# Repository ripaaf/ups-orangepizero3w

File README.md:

# ups-orangepizero3w
trying making a pcb ups for orangepi (its bad)

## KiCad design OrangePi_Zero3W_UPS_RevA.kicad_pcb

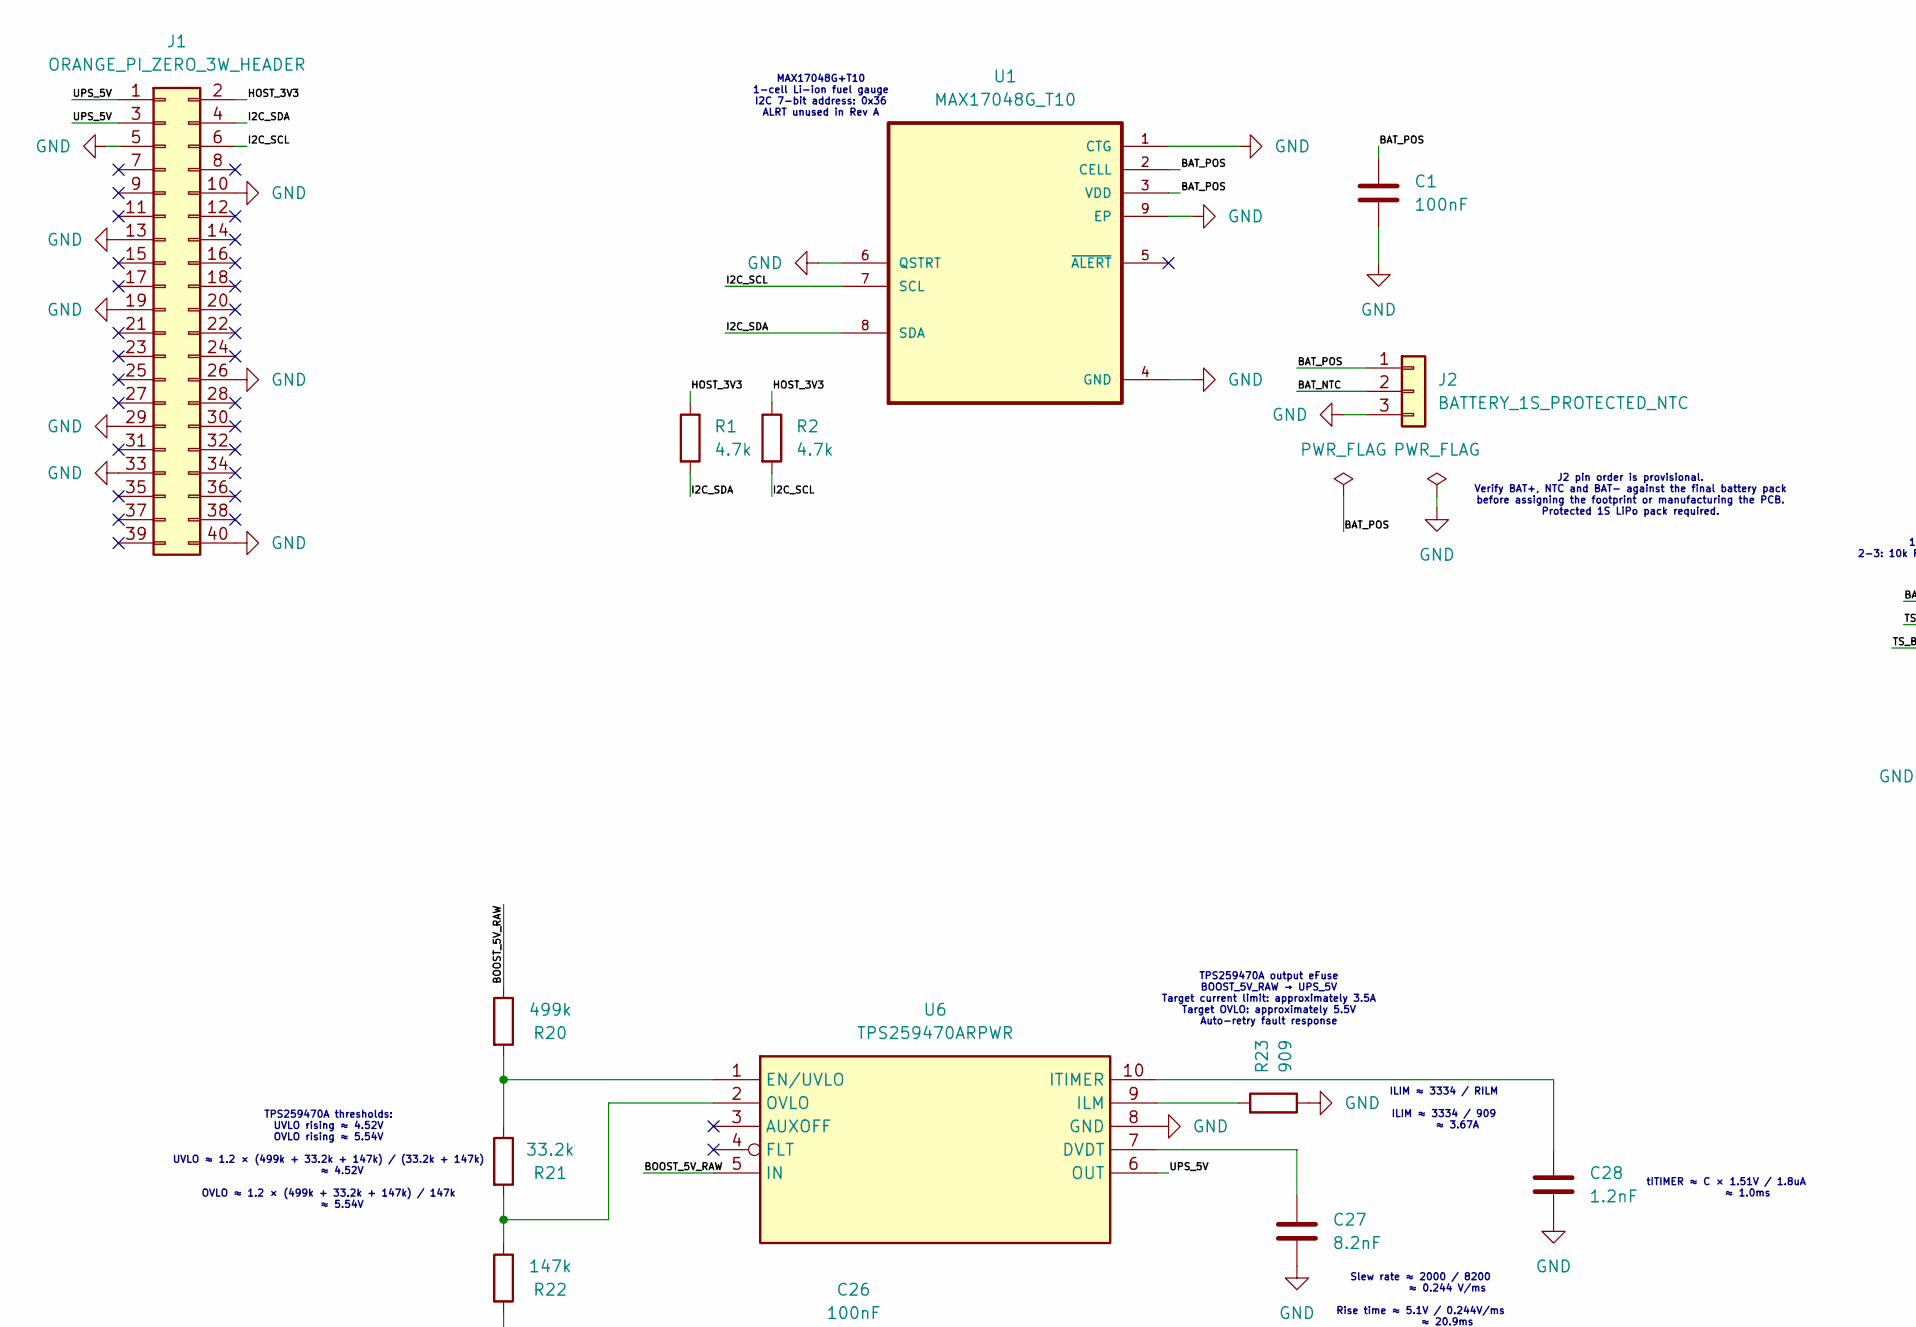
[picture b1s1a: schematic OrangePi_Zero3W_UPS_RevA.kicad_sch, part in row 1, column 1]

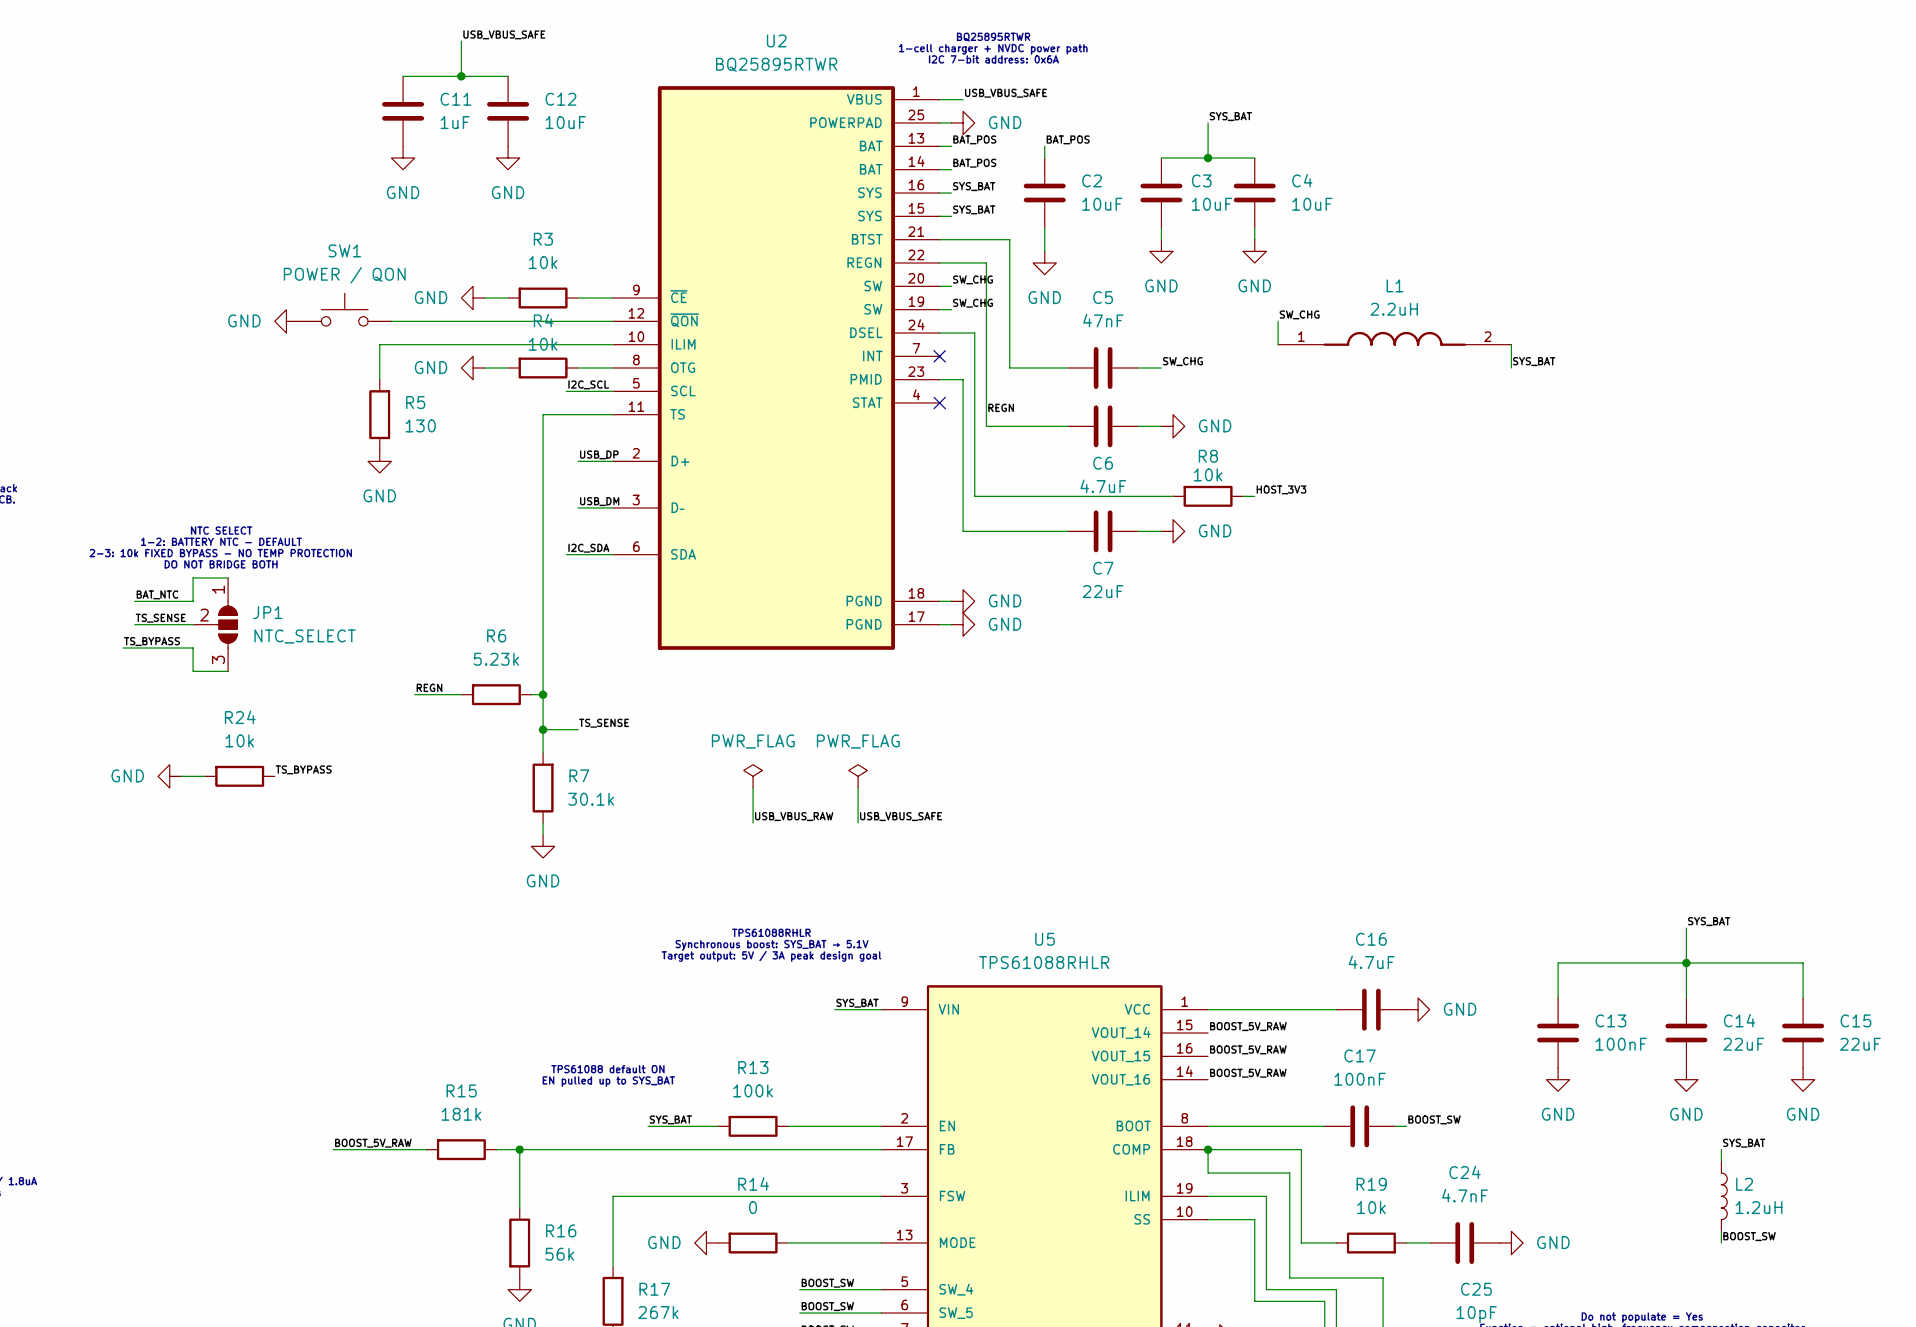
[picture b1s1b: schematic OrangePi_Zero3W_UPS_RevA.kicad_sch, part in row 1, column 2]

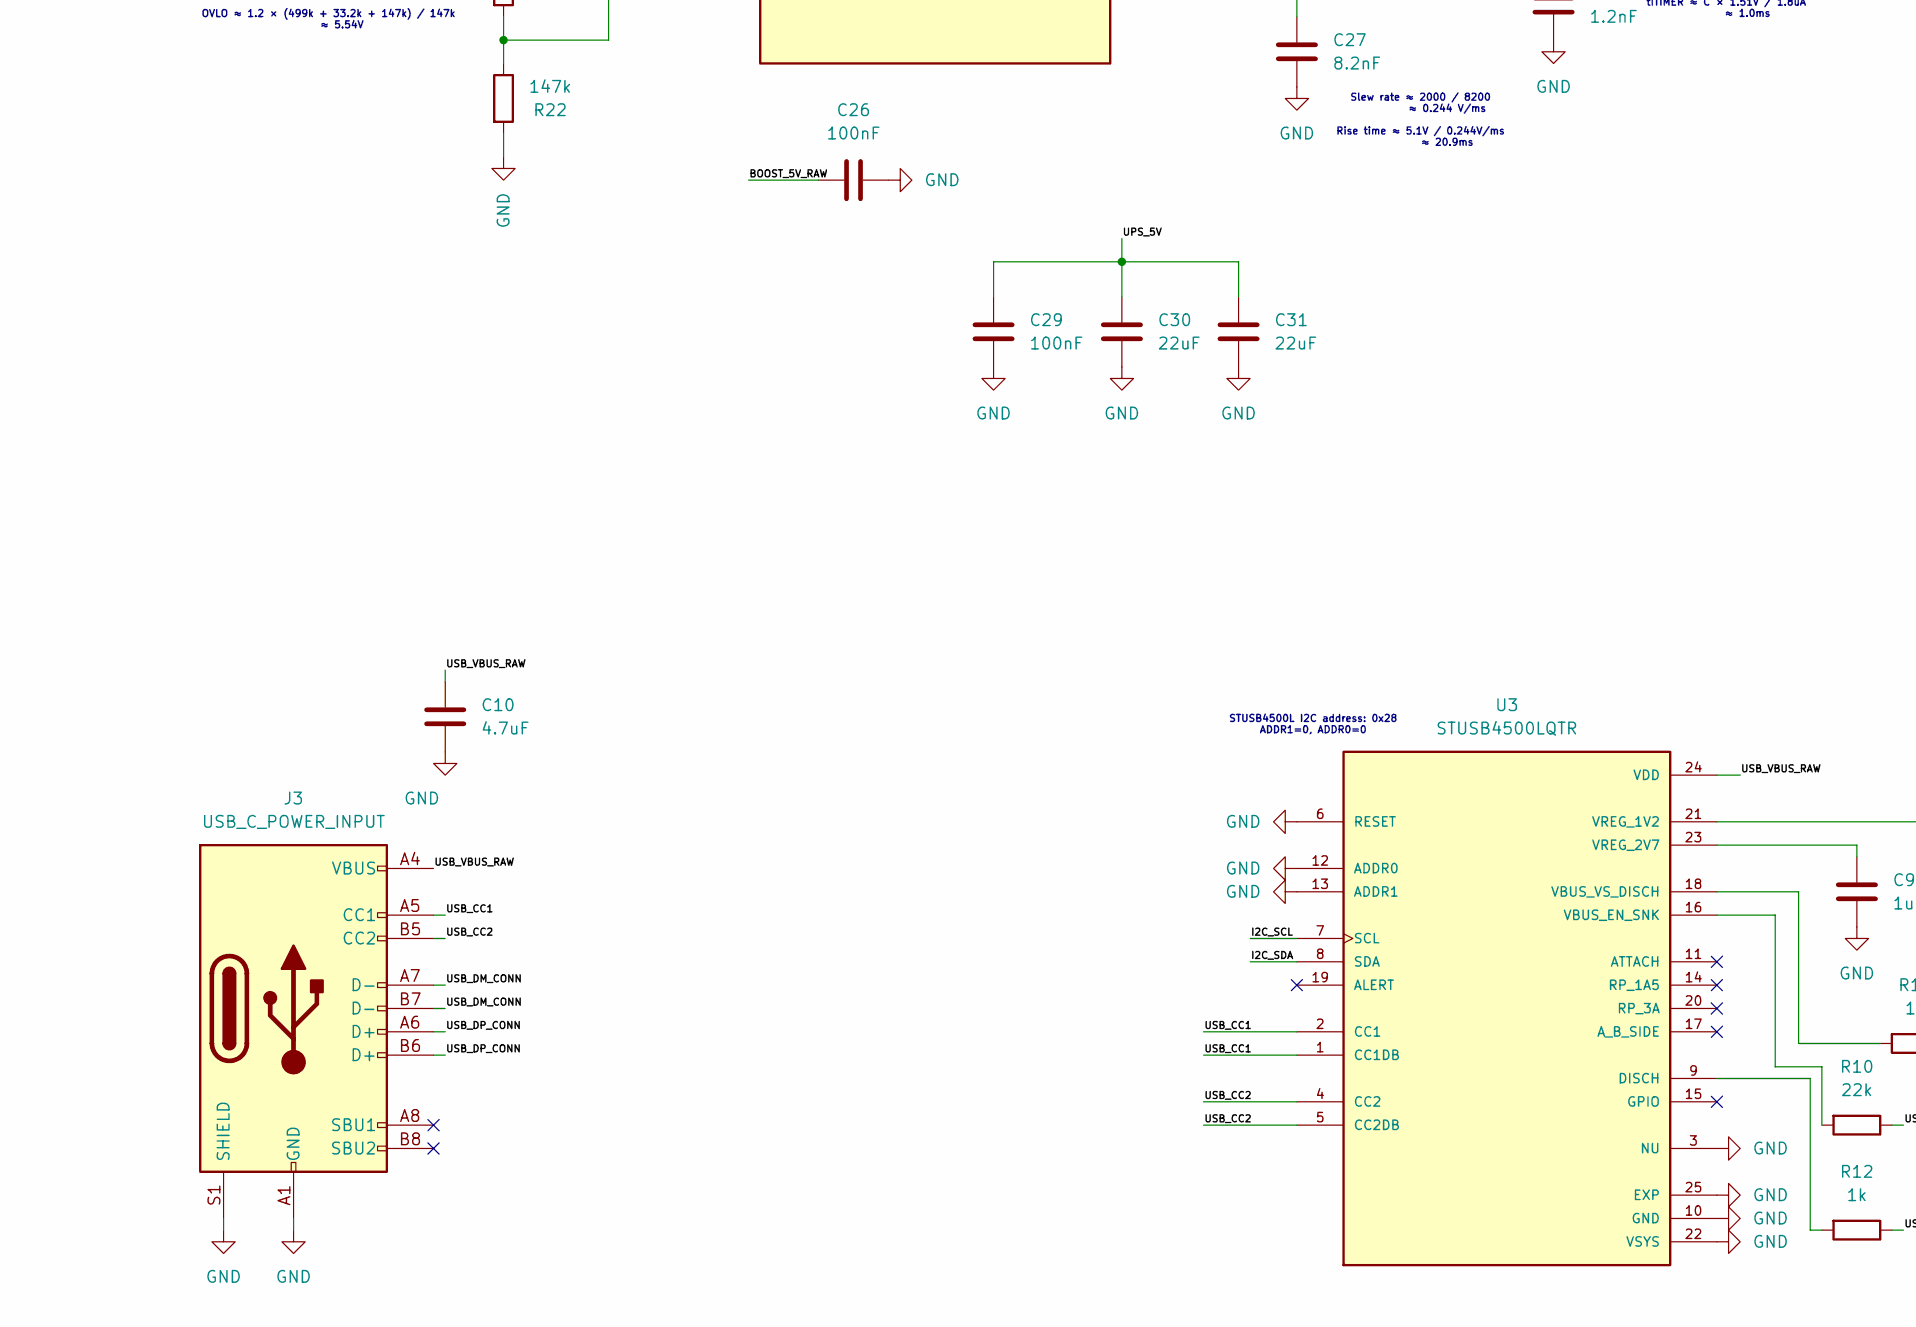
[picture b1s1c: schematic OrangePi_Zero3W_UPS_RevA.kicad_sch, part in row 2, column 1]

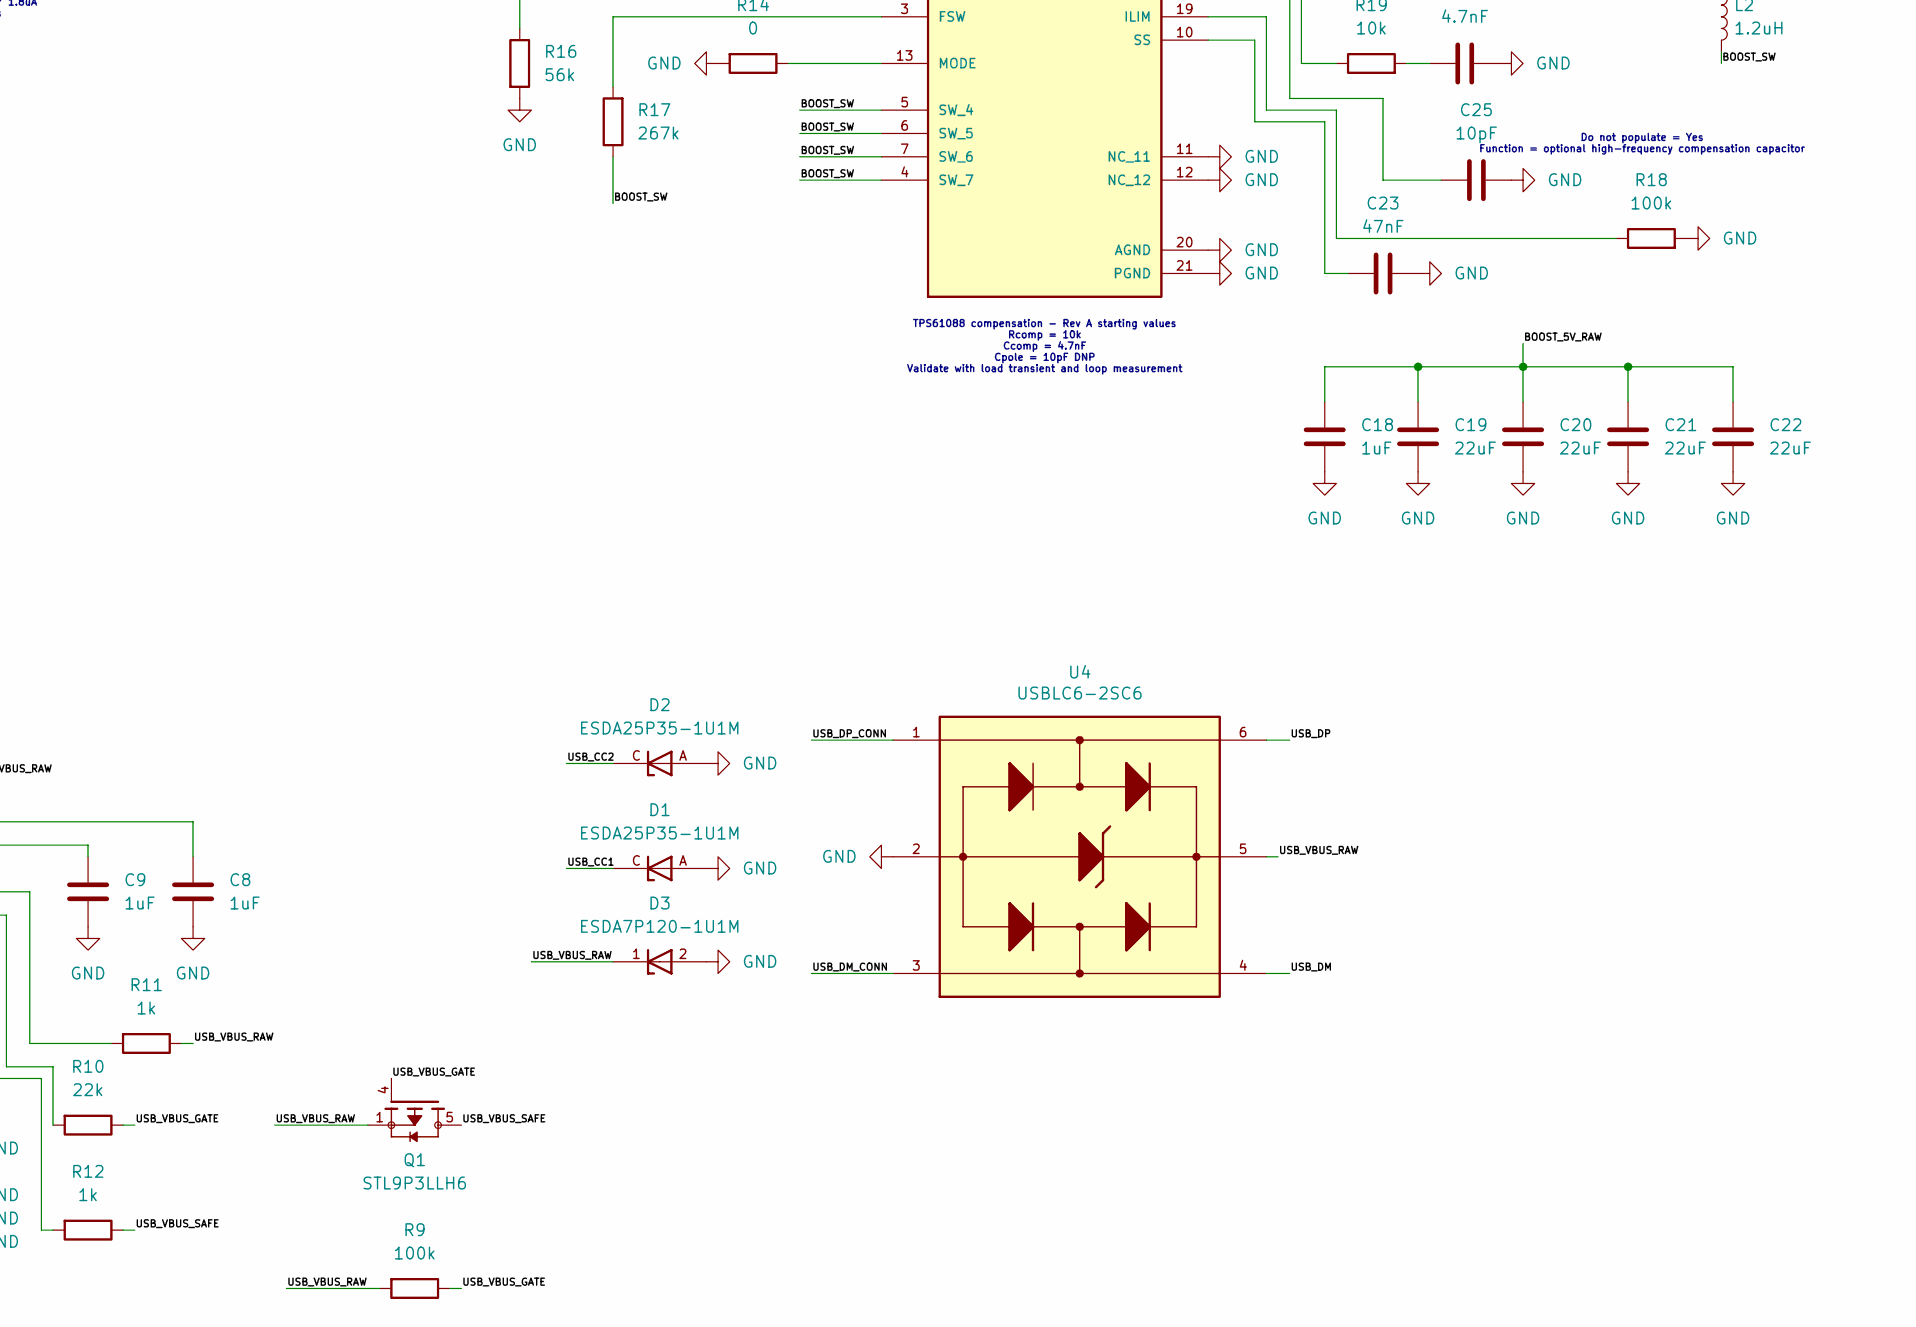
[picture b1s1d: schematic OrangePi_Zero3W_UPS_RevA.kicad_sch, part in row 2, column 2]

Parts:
C1: 100nF; C_0603_1608Metric
C2, C3, C4: 10uF; C_0805_2012Metric
C5: 47nF; C_0402_1005Metric; Voltage minimum 16V
C6, C16: 4.7uF; C_0603_1608Metric; Voltage 10V minimum
C7: 22uF; C_0805_2012Metric; Voltage 25V; MPN GRM21BR61E226ME44
C8, C9: 1uF; C_0603_1608Metric; Voltage 6.3V or higher
C10: 4.7uF; C_0805_2012Metric; Voltage rating minimal 10V
C11: 1uF; C_0805_2012Metric; Voltage rating minimal 25V; MPN GRM219R71E105KA88D
C12: 10uF; C_0805_2012Metric; Voltage rating minimal 25V; MPN C2012X5R1E106K125AB
C13, C26, C29: 100nF; C_0603_1608Metric; Voltage 10V minimum
C14, C15, C19, C20, C21, C22, C30, C31: 22uF; C_1206_3216Metric; Voltage 10V minimum
C17: 100nF; C_0402_1005Metric; Voltage 16V minimum
C18: 1uF; C_0603_1608Metric; Voltage 10V minimum
C23: 47nF; C_0402_1005Metric; Voltage 10V minimum
C24: 4.7nF; C_0402_1005Metric; Voltage 10V minimum
C25: 10pF; C_0402_1005Metric; Voltage 25V atau lebih
C27: 8.2nF; C_0402_1005Metric; Voltage 10V minimum
C28: 1.2nF; C_0402_1005Metric; Voltage 10V minimum
D1, D2: ESDA25P35-1U1M; TVS_ESDA25P35-1U1M; PARTREV 2
D3: ESDA7P120-1U1M; TVS_ESDA7P120-1U1M; PARTREV 4
J1: ORANGE_PI_ZERO_3W_HEADER; PinSocket_2x20_P2.54mm_Vertical
J2: BATTERY_1S_PROTECTED_NTC; JST_PH_S3B-PH-SM4-TB_1x03-1MP_P2.00mm_Horizontal
J3: USB_C_POWER_INPUT; USB_C_Receptacle_JAE_DX07S016JA1R1500; MPN DX07S016JA1R1500
JP1: NTC_SELECT; SolderJumper-3_P1.3mm_Open_Pad1.0x1.5mm_NumberLabels
L1: 2.2uH; INDM686X647X300N; PARTREV 16-Oct-2020
L2: 1.2uH; Coilcraft_XGL6030; Tolerance ±20%; MPN XGL6030-122MEC
Q1: STL9P3LLH6; TRANS_STL9P3LLH6; PARTREV 3
R1, R2: 4.7k; R_0603_1608Metric
R3, R4, R8: 10k; R_0603_1608Metric
R5: 130; R_0603_1608Metric; Tolerance 1%
R6: 5.23k; R_0603_1608Metric; Tolerance 1%
R7: 30.1k; R_0603_1608Metric; Tolerance 1%
R9, R13: 100k; R_0603_1608Metric
R10: 22k; R_0603_1608Metric
R11, R12: 1k; R_0603_1608Metric
R14: 0; R_0603_1608Metric
R15: 181k; R_0603_1608Metric; tolerance 1%
R16: 56k; R_0603_1608Metric; tolerance 1%
R17: 267k; R_0603_1608Metric; tolerance 1%
R18: 100k; R_0603_1608Metric; tolerance 1%
R19: 10k; R_0603_1608Metric; tolerance 1%
R20: 499k; R_0603_1608Metric; tolerance 1%
R21: 33.2k; R_0603_1608Metric; tolerance 1%
R22: 147k; R_0603_1608Metric; tolerance 1%
R23: 909; R_0603_1608Metric; tolerance 1%
R24: 10k; R_0603_1608Metric; Tolerance 1%
SW1: POWER / QON; SW_B3U-1000P
U1: MAX17048G_T10; SON50P200X200X80-9N; MPN MAX17048G+T10
U2: BQ25895RTWR; QFN50P400X400X80-25N; MPN BQ25895RTWR
U3: STUSB4500LQTR; QFN50P400X400X100-25N; PARTREV 4
U4: USBLC6-2SC6; SOT95P280X145-6N; MPN USBLC6-2SC6
U5: TPS61088RHLR; IC_TPS61088RHLR; PARTREV 4219071/A 05/2017; LCSC Part # C87357
U6: TPS259470ARPWR; TPS259470ARPWR_RPW0010A; MPN TPS259470ARPWR

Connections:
/BAT_NTC: J2.2, JP1.1 (A)
/BAT_POS: C1.1, C2.1, J2.1, U1.2 (CELL), U1.3 (VDD), U2.13 (BAT), U2.14 (BAT)
/BOOST_5V_RAW: C18.1, C19.1, C20.1, C21.1, C22.1, C26.2, R15.2, R20.1, U5.14 (VOUT_16), U5.15 (VOUT_14), U5.16 (VOUT_15), U6.5 (IN)
/BOOST_SW: C17.1, L2.2, R17.1, U5.4 (SW_7), U5.5 (SW_4), U5.6 (SW_5), U5.7 (SW_6)
/HOST_3V3: J1.2, R1.1, R2.1, R8.1
/I2C_SCL: J1.6, R2.2, U1.7 (SCL), U2.5 (SCL), U3.7 (SCL)
/I2C_SDA: J1.4, R1.2, U1.8 (SDA), U2.6 (SDA), U3.8 (SDA)
/REGN: C6.2, R6.2, U2.22 (REGN)
/SW_CHG: C5.1, L1.1, U2.19 (SW), U2.20 (SW)
/SYS_BAT: C3.1, C4.1, C13.1, C14.1, C15.1, L1.2, L2.1, R13.2, U2.15 (SYS), U2.16 (SYS), U5.9 (VIN)
/TS_BYPASS: JP1.3 (B), R24.1
/TS_SENSE: JP1.2 (C), R6.1, R7.2, U2.11 (TS)
/UPS_5V: C29.2, C30.2, C31.2, J1.1, J1.3, U6.6 (OUT)
/USB_CC1: D1.C, J3.A5 (CC1), U3.1 (CC1DB), U3.2 (CC1)
/USB_CC2: D2.C, J3.B5 (CC2), U3.4 (CC2), U3.5 (CC2DB)
/USB_DM: U2.3 (D–), U4.4
/USB_DM_CONN: J3.A7 (D-), J3.B7 (D-), U4.3
/USB_DP: U2.2 (D+), U4.6
/USB_DP_CONN: J3.A6 (D+), J3.B6 (D+), U4.1
/USB_VBUS_GATE: Q1.4, R9.1, R10.1
/USB_VBUS_RAW: C10.1, D3.1, J3.A4 (VBUS), J3.A9 (VBUS), J3.B4 (VBUS), J3.B9 (VBUS), Q1.1, Q1.2, Q1.3, R9.2, R11.1, U3.24 (VDD), U4.5
/USB_VBUS_SAFE: C11.1, C12.1, Q1.5, Q1.5_1, Q1.5_2, R12.1, U2.1 (VBUS)
GND: C1.2, C2.2, C3.2, C4.2, C6.1, C7.2, C8.2, C9.2, C10.2, C11.2, C12.2, C13.2, C14.2, C15.2, C16.2, C18.2, C19.2, C20.2, C21.2, C22.2, C23.1, C24.1, C25.1, C26.1, C27.1, C28.1, C29.1, C30.1, C31.1, D1.A, D2.A, D3.2, J1.5, J1.10, J1.13, J1.19, J1.26, J1.29, J1.33, J1.40, J2.3, J3.A1 (GND), J3.A12 (GND), J3.B1 (GND), J3.B12 (GND), J3.S1 (SHIELD), R3.2, R4.2, R5.1, R7.1, R14.2, R16.2, R18.2, R22.2, R23.1, R24.2, SW1.1, U1.1 (CTG), U1.4 (GND), U1.6 (QSTRT), U1.9 (EP), U2.17 (PGND), U2.18 (PGND), U2.25 (POWERPAD), U3.3 (NU), U3.6 (RESET), U3.10 (GND), U3.12 (ADDR0), U3.13 (ADDR1), U3.22 (VSYS), U3.25 (EXP), U4.2, U5.11 (NC_11), U5.12 (NC_12), U5.20 (AGND), U5.21 (PGND), U6.8 (GND)
unnamed: C24.2, R19.2
unnamed: C5.2, U2.21 (BTST)
unnamed: R8.2, U2.24 (DSEL)
unnamed: R5.2, U2.10 (ILIM)
unnamed: R4.1, U2.8 (OTG)
unnamed: C7.1, U2.23 (PMID)
unnamed: R3.1, U2.9 (~CE)
unnamed: SW1.2, U2.12 (~QON)
unnamed: R12.2, U3.9 (DISCH)
unnamed: R10.2, U3.16 (VBUS_EN_SNK)
unnamed: R11.2, U3.18 (VBUS_VS_DISCH)
unnamed: C8.1, U3.21 (VREG_1V2)
unnamed: C9.1, U3.23 (VREG_2V7)
unnamed: C17.2, U5.8 (BOOT)
unnamed: C25.2, R19.1, U5.18 (COMP)
unnamed: R13.1, U5.2 (EN)
unnamed: R15.1, R16.1, U5.17 (FB)
unnamed: R17.2, U5.3 (FSW)
unnamed: R18.1, U5.19 (ILIM)
unnamed: R14.1, U5.13 (MODE)
unnamed: C23.2, U5.10 (SS)
unnamed: C16.1, U5.1 (VCC)
unnamed: C27.2, U6.7 (DVDT)
unnamed: R20.2, R21.1, U6.1 (EN/UVLO)
unnamed: R23.2, U6.9 (ILM)
unnamed: C28.2, U6.10 (ITIMER)
unnamed: R21.2, R22.1, U6.2 (OVLO)

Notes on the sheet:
NTC SELECT 1-2: BATTERY NTC - DEFAULT 2-3: 10k FIXED BYPASS - NO TEMP PROTECTION DO NOT BRIDGE BOTH
TPS61088RHLR Synchronous boost: SYS_BAT → 5.1V Target output: 5V / 3A peak design goal
STUSB4500L I2C address: 0x28 ADDR1=0, ADDR0=0
Slew rate ≈ 2000 / 8200 ≈ 0.244 V/ms Rise time ≈ 5.1V / 0.244V/ms ≈ 20.9ms
Do not populate = Yes Function = optional high-frequency compensation capacitor
J2 pin order is provisional. Verify BAT+, NTC and BAT- against the final battery pack before assigning the footprint or manufacturing the PCB. Protected 1S LiPo pack required.
TPS61088 default ON EN pulled up to SYS_BAT
TPS259470A output eFuse BOOST_5V_RAW → UPS_5V Target current limit: approximately 3.5A Target OVLO: approximately 5.5V Auto-retry fault response
tITIMER ≈ C × 1.51V / 1.8uA ≈ 1.0ms
ILIM ≈ 3334 / RILM ILIM ≈ 3334 / 909 ≈ 3.67A
TPS259470A thresholds: UVLO rising ≈ 4.52V OVLO rising ≈ 5.54V UVLO ≈ 1.2 × (499k + 33.2k + 147k) / (33.2k + 147k) ≈ 4.52V OVLO ≈ 1.2 × (499k + 33.2k + 147k) / 147k ≈ 5.54V
TPS61088 compensation - Rev A starting values Rcomp = 10k Ccomp = 4.7nF Cpole = 10pF DNP Validate with load transient and loop measurement
BQ25895RTWR 1-cell charger + NVDC power path I2C 7-bit address: 0x6A
MAX17048G+T10 1-cell Li-ion fuel gauge I2C 7-bit address: 0x36 ALRT unused in Rev A

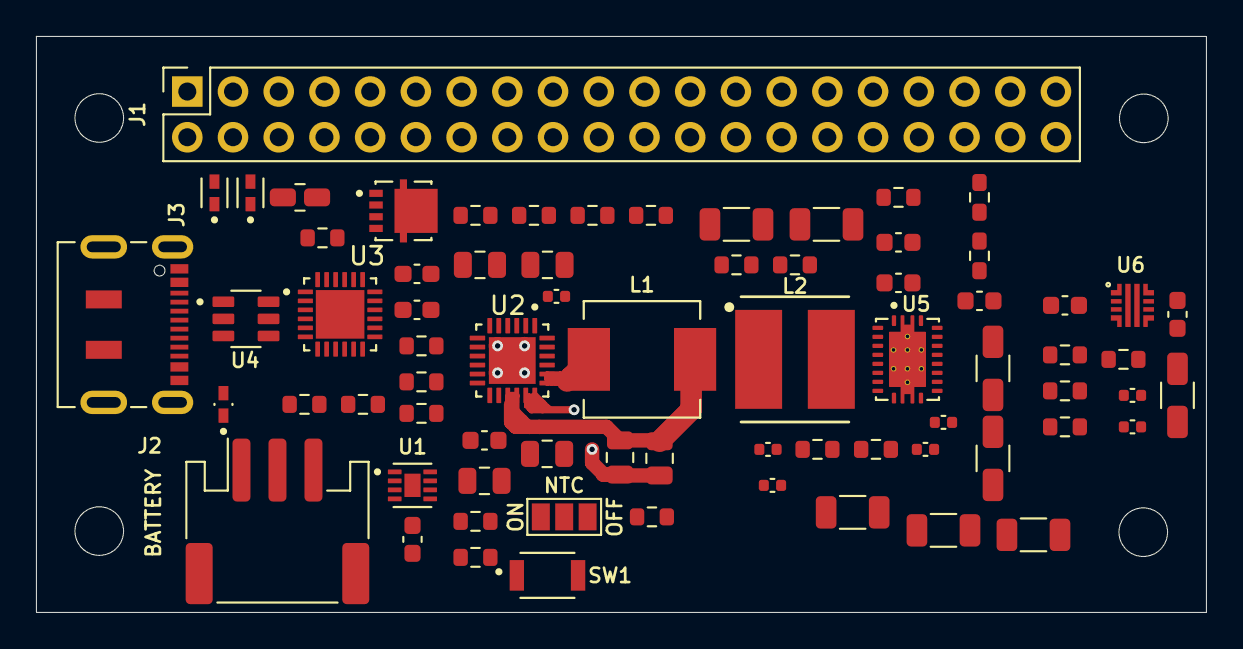
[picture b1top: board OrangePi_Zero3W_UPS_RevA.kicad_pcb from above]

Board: 4 copper layers, 65.0 x 32.0 mm, 72 parts (0 on the bottom side), 50 nets.
